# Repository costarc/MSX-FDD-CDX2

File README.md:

# MSX-FDD-CDX2
MSX Floppy Disk Drive Clone of CDX-2 (Access by I/O Ports)

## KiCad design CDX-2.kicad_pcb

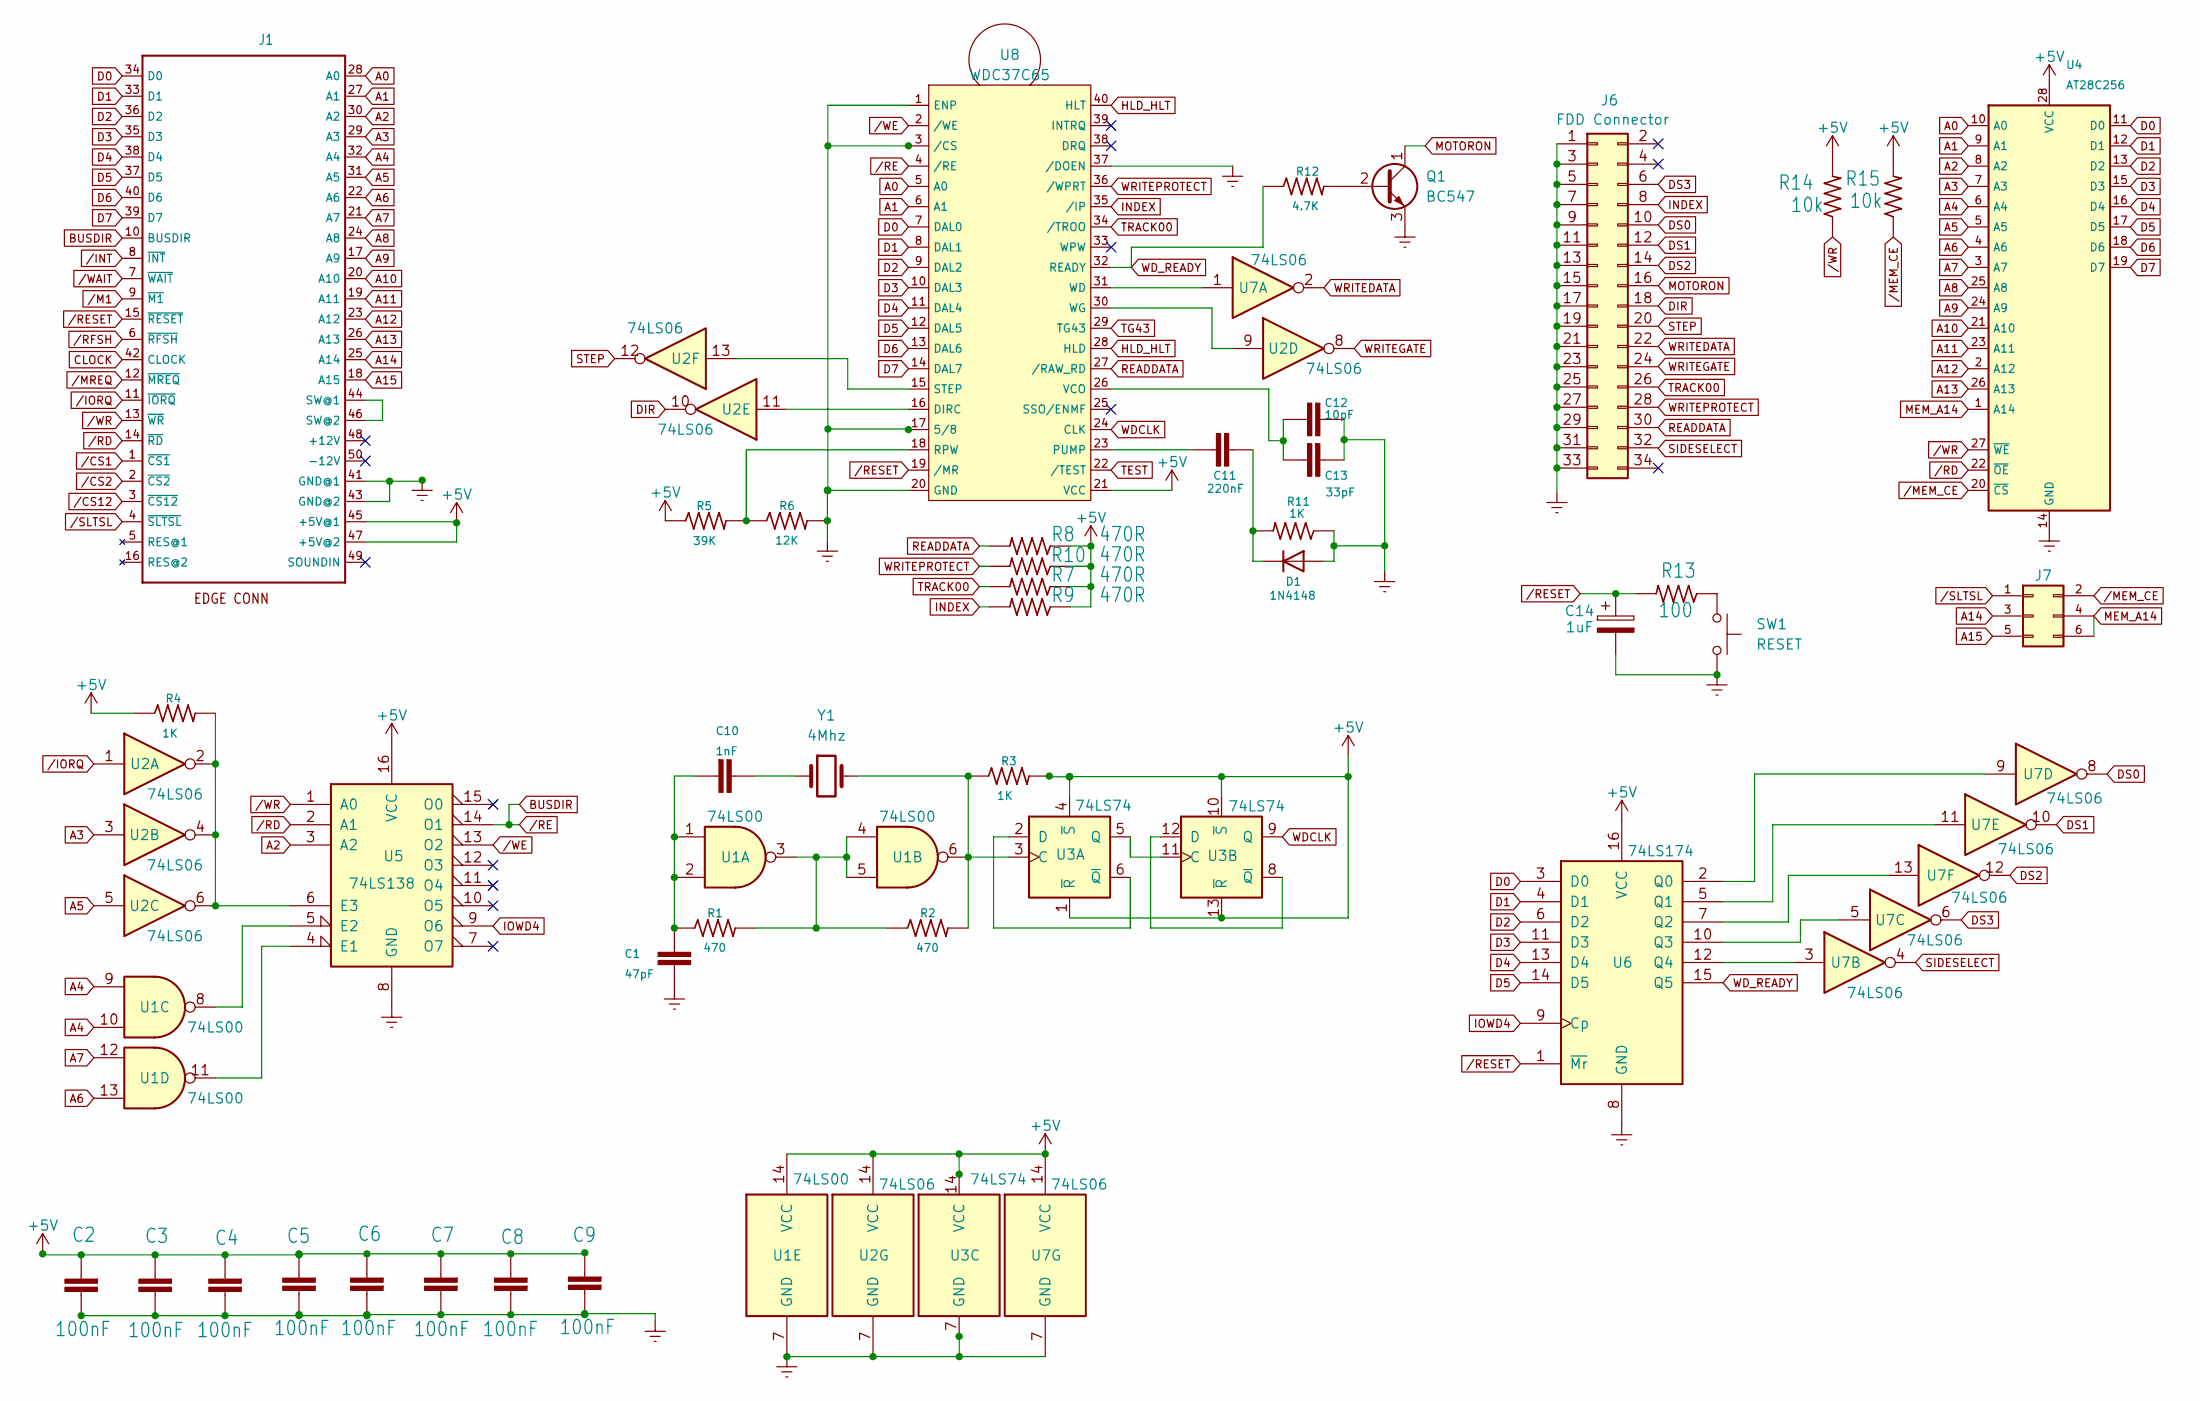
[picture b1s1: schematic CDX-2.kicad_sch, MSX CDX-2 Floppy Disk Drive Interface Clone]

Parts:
C1: 47pF; C_Disc_D3.0mm_W1.6mm_P2.50mm
C2, C3, C4, C5, C6, C7, C8, C9: 100nF; C_Disc_D3.0mm_W1.6mm_P2.50mm
C10: 1nF; C_Disc_D3.0mm_W1.6mm_P2.50mm
C11: 220nF; C_Disc_D3.0mm_W1.6mm_P2.50mm
C12: 10pF; C_Disc_D3.0mm_W1.6mm_P2.50mm
C13: 33pF; C_Disc_D3.0mm_W1.6mm_P2.50mm
C14: 1uF; CP_Radial_D4.0mm_P1.50mm
D1: 1N4148; D_DO-35_SOD27_P7.62mm_Horizontal
J1: MSXCART1; MSX_CART_SW_Official
J6: FDD Connector; PinHeader_2x17_P2.54mm_Horizontal
J7: ROM_SWITCH; PinHeader_2x03_P2.54mm_Horizontal
Q1: BC547; TO-92_Inline
R1, R2: 470; R_Axial_DIN0207_L6.3mm_D2.5mm_P7.62mm_Horizontal
R3, R4, R11: 1K; R_Axial_DIN0207_L6.3mm_D2.5mm_P7.62mm_Horizontal
R5: 39K; R_Axial_DIN0207_L6.3mm_D2.5mm_P7.62mm_Horizontal
R6: 12K; R_Axial_DIN0207_L6.3mm_D2.5mm_P7.62mm_Horizontal
R7, R8, R9, R10: 470R; R_Axial_DIN0207_L6.3mm_D2.5mm_P7.62mm_Horizontal
R12: 4.7K; R_Axial_DIN0207_L6.3mm_D2.5mm_P7.62mm_Horizontal
R13: 100; R_Axial_DIN0207_L6.3mm_D2.5mm_P7.62mm_Horizontal
R14, R15: 10k; R_Axial_DIN0207_L6.3mm_D2.5mm_P7.62mm_Horizontal
SW1: RESET; SW_Tactile_SPST_Angled_PTS645Vx31-2LFS
U1: 74LS00; DIP-14_W7.62mm
U2, U7: 74LS06; DIP-14_W7.62mm
U3: 74LS74; DIP-14_W7.62mm
U4: AT28C256; DIP-28_W15.24mm
U5: 74LS138; DIP-16_W7.62mm
U6: 74LS174; DIP-16_W7.62mm
U8: WDC37C65; DIP-40_W15.24mm
Y1: 4Mhz; Crystal_HC49-U_Vertical

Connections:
+5V: C2.2, C3.2, C4.2, C5.2, C6.2, C7.2, C8.2, C9.2, J1.45 (+5V@1), J1.47 (+5V@2), R3.2, R4.1, R5.1, R7.1, R8.1, R9.1, R10.1, R14.2, R15.2, U1.14 (VCC), U2.14 (VCC), U3.1 (~R), U3.4 (~S), U3.10 (~S), U3.13 (~R), U3.14 (VCC), U4.28 (VCC), U5.16 (VCC), U6.16 (VCC), U7.14 (VCC), U8.21 (VCC)
A0: J1.28 (A0), U4.10 (A0), U8.5 (A0)
A1: J1.27 (A1), U4.9 (A1), U8.6 (A1)
A2: J1.30 (A2), U4.8 (A2), U5.3 (A2)
A3: J1.29 (A3), U2.3, U4.7 (A3)
A4: J1.32 (A4), U1.10, U4.6 (A4)
A5: J1.31 (A5), U2.5, U4.5 (A5)
A6: J1.22 (A6), U1.13, U4.4 (A6)
A7: J1.21 (A7), U1.12, U4.3 (A7)
A8: J1.24 (A8), U4.25 (A8)
A9: J1.17 (A9), U4.24 (A9)
A10: J1.20 (A10), U4.21 (A10)
A11: J1.19 (A11), U4.23 (A11)
A12: J1.23 (A12), U4.2 (A12)
A13: J1.26 (A13), U4.26 (A13)
A14: J1.25 (A14), J7.3
A15: J1.18 (A15), J7.5
CLOCK: J1.42 (CLOCK)
D0: J1.34 (D0), U4.11 (D0), U6.3 (D0), U8.7 (DAL0)
D1: J1.33 (D1), U4.12 (D1), U6.4 (D1), U8.8 (DAL1)
D2: J1.36 (D2), U4.13 (D2), U6.6 (D2), U8.9 (DAL2)
D3: J1.35 (D3), U4.15 (D3), U6.11 (D3), U8.10 (DAL3)
D4: J1.38 (D4), U4.16 (D4), U6.13 (D4), U8.11 (DAL4)
D5: J1.37 (D5), U4.17 (D5), U6.14 (D5), U8.12 (DAL5)
D6: J1.40 (D6), U4.18 (D6), U8.13 (DAL6)
D7: J1.39 (D7), U4.19 (D7), U8.14 (DAL7)
DS0: J6.10, U7.8
DS1: J6.12, U7.10
DS2: J6.14, U7.12
DS3: J6.6, U7.6
GNDREF: C1.2, C2.1, C3.1, C4.1, C5.1, C6.1, C7.1, C8.1, C9.1, C12.1, C13.1, C14.2, D1.2 (A), J1.41 (GND@1), J1.43 (GND@2), J6.1, J6.3, J6.5, J6.7, J6.9, J6.11, J6.13, J6.15, J6.17, J6.19, J6.21, J6.23, J6.25, J6.27, J6.29, J6.31, J6.33, Q1.3 (E), R6.2, R11.1, SW1.2, U1.7 (GND), U2.7 (GND), U3.7 (GND), U4.14 (GND), U5.8 (GND), U6.8 (GND), U7.7 (GND), U8.1 (ENP), U8.3 (/CS), U8.17 (5/8), U8.20 (GND), U8.37 (/DOEN)
HLD_HLT: U8.28 (HLD), U8.40 (HLT)
INDEX: J6.8, R9.2, U8.35 (/IP)
IOWD4: U5.9 (O6), U6.9 (Cp)
MEM_A14: J7.4, J7.6, U4.1 (A14)
MOTORON: J6.16, Q1.1 (C)
unnamed: C10.1, Y1.1
unnamed: C1.1, C10.2, R1.1, U1.1, U1.2
unnamed: C11.1, D1.1 (K), R11.2
unnamed: J1.44 (SW@1), J1.46 (SW@2)
unnamed: Q1.2 (B), R12.2
unnamed: R13.1, SW1.1
unnamed: R1.2, R2.1, U1.3, U1.4, U1.5
unnamed: U3.2 (D), U3.6 (~Q)
unnamed: U3.5 (Q), U3.11 (C)
unnamed: U3.8 (~Q), U3.12 (D)
unnamed: U1.11, U5.4 (E1)
unnamed: U1.8, U5.5 (E2)
unnamed: R4.2, U2.2, U2.4, U2.6, U5.6 (E3)
unnamed: U6.2 (Q0), U7.9
unnamed: U6.5 (Q1), U7.11
unnamed: U6.7 (Q2), U7.13
unnamed: U6.10 (Q3), U7.5
unnamed: U6.12 (Q4), U7.3
unnamed: U2.13, U8.15 (STEP)
unnamed: U2.11, U8.16 (DIRC)
unnamed: R5.2, R6.1, U8.18 (RPW)
unnamed: C11.2, U8.23 (PUMP)
unnamed: C12.2, C13.2, U8.26 (VCO)
unnamed: U2.9, U8.30 (WG)
unnamed: U7.1, U8.31 (WD)
unnamed: R2.2, R3.1, U1.6, U3.3 (C), Y1.2
READDATA: J6.30, R8.2, U8.27 (/RAW_RD)
SIDESELECT: U7.4
STEP: J6.20, U2.12
TEST: U8.22 (/TEST)
TG43: U8.29 (TG43)
TRACK00: R7.2, U8.34 (/TROO)
WDCLK: U3.9 (Q), U8.24 (CLK)
WD_READY: R12.1, U6.15 (Q5), U8.32 (READY)
WRITEDATA: J6.22, U7.2
WRITEGATE: U2.8
WRITEPROTECT: J6.28, R10.2, U8.36 (/WPRT)
/CS1: J1.1 (~CS1)
/CS2: J1.2 (~CS2)
/CS12: J1.3 (~CS12)
/INT: J1.8 (~INT)
/IORQ: J1.11 (~IORQ), U2.1
/M1: J1.9 (~M1)
/MEM_CE: J7.2, R15.1, U4.20 (~CS)
/MREQ: J1.12 (~MREQ)
/RD: J1.14 (~RD), U4.22 (~OE), U5.2 (A1)
/RE: J1.10 (BUSDIR), U5.14 (O1), U8.4 (/RE)
/RESET: C14.1, J1.15 (~RESET), R13.2, U6.1 (~Mr), U8.19 (/MR)
/RFSH: J1.6 (~RFSH)
/SLTSL: J1.4 (~SLTSL), J7.1
/WAIT: J1.7 (~WAIT)
/WE: U5.13 (O2), U8.2 (/WE)
/WR: J1.13 (~WR), R14.1, U4.27 (~WE), U5.1 (A0)

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
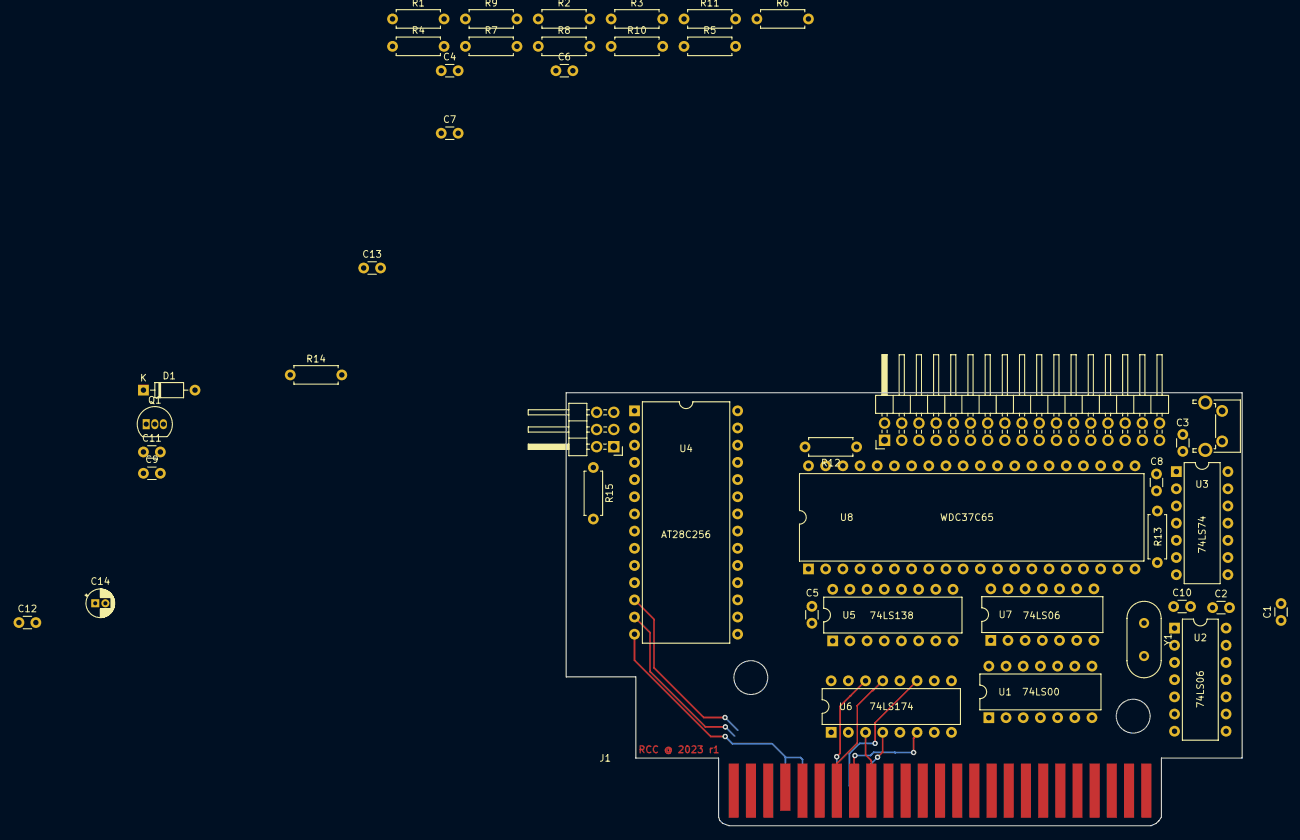
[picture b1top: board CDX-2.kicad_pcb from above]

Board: 2 copper layers, 99.9 x 64.0 mm, 44 parts (0 on the bottom side), 76 nets.

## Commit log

2023-05-29 Initial project
